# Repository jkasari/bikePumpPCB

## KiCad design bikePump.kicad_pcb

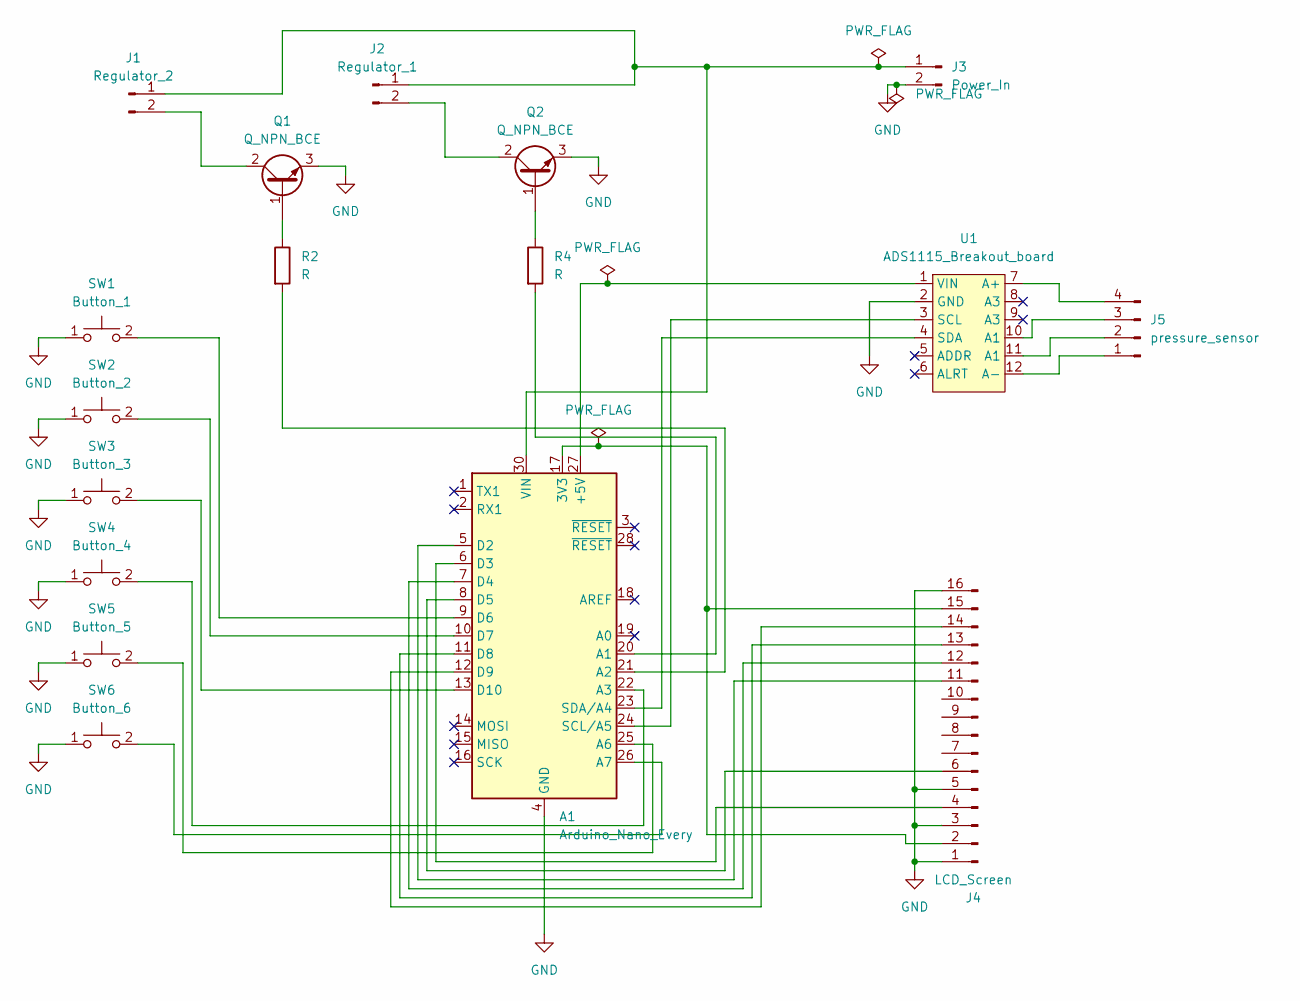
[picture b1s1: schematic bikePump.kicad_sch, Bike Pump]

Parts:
A1: Arduino_Nano_Every; Arduino_Nano
J1: Regulator_2; SolderWire-0.5sqmm_1x02_P4.6mm_D0.9mm_OD2.1mm
J2: Regulator_1; SolderWire-0.5sqmm_1x02_P4.6mm_D0.9mm_OD2.1mm
J3: Power_In; SolderWire-0.5sqmm_1x02_P4.6mm_D0.9mm_OD2.1mm
J4: LCD_Screen
J5: pressure_sensor; SolderWire-0.25sqmm_1x04_P4.5mm_D0.65mm_OD2mm
Q1, Q2: Q_NPN_BCE; DSS60601MZ4-13_NPN_Transitor
R2, R4: R; R_Axial_DIN0207_L6.3mm_D2.5mm_P10.16mm_Horizontal
SW1: Button_1; SW_PUSH_6mm
SW2: Button_2; SW_PUSH_6mm
SW3: Button_3; SW_PUSH_6mm
SW4: Button_4; SW_PUSH_6mm
SW5: Button_5; SW_PUSH_6mm
SW6: Button_6; SW_PUSH_6mm
U1: ADS1115_Breakout_board; AdaFruit_ADS1115_Board

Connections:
GND: A1.4 (GND), A1.29 (GND), J3.2 (+), J4.1, J4.3, J4.5, J4.16, Q1.3 (E), Q2.3 (E), SW1.1, SW2.1 (A), SW3.1, SW4.1, SW5.1, SW6.1, U1.2 (GND); also elsewhere on the board
unnamed 1: A1.5 (D2), J4.11; also elsewhere on the board
unnamed 2: A1.6 (D3), J4.4; also elsewhere on the board
unnamed 3: A1.7 (D4), J4.12; also elsewhere on the board
unnamed 4: A1.8 (D5), J4.6; also elsewhere on the board
unnamed: A1.9 (D6), SW1.2
unnamed: A1.10 (D7), SW2.2
unnamed 7: A1.11 (D8), J4.13; also elsewhere on the board
unnamed 8: A1.12 (D9), J4.14; also elsewhere on the board
unnamed: A1.13 (D10), SW3.2
unnamed 10: A1.17 (3V3), J4.2, J4.15; also elsewhere on the board
unnamed: A1.20 (A1), R4.2
unnamed: A1.21 (A2), R2.2
unnamed: A1.22 (A3), SW4.2
unnamed: A1.23 (SDA/A4), U1.4 (SDA)
unnamed: A1.24 (SCL/A5), U1.3 (SCL)
unnamed: A1.25 (A6), SW5.2
unnamed: A1.26 (A7), SW6.2
unnamed: A1.27 (+5V), U1.1 (VIN)
unnamed: A1.30 (VIN), J1.1, J2.1, J3.1 (-)
unnamed: J2.2, Q2.2 (C)
unnamed: J5.1, U1.12 (A-)
unnamed: J5.2, U1.11 (A1)
unnamed: J5.3, U1.10 (A1)
unnamed: J5.4, U1.7 (A+)
unnamed: Q1.1 (B), R2.1
unnamed: J1.2, Q1.2 (C)
unnamed: Q2.1 (B), R4.1

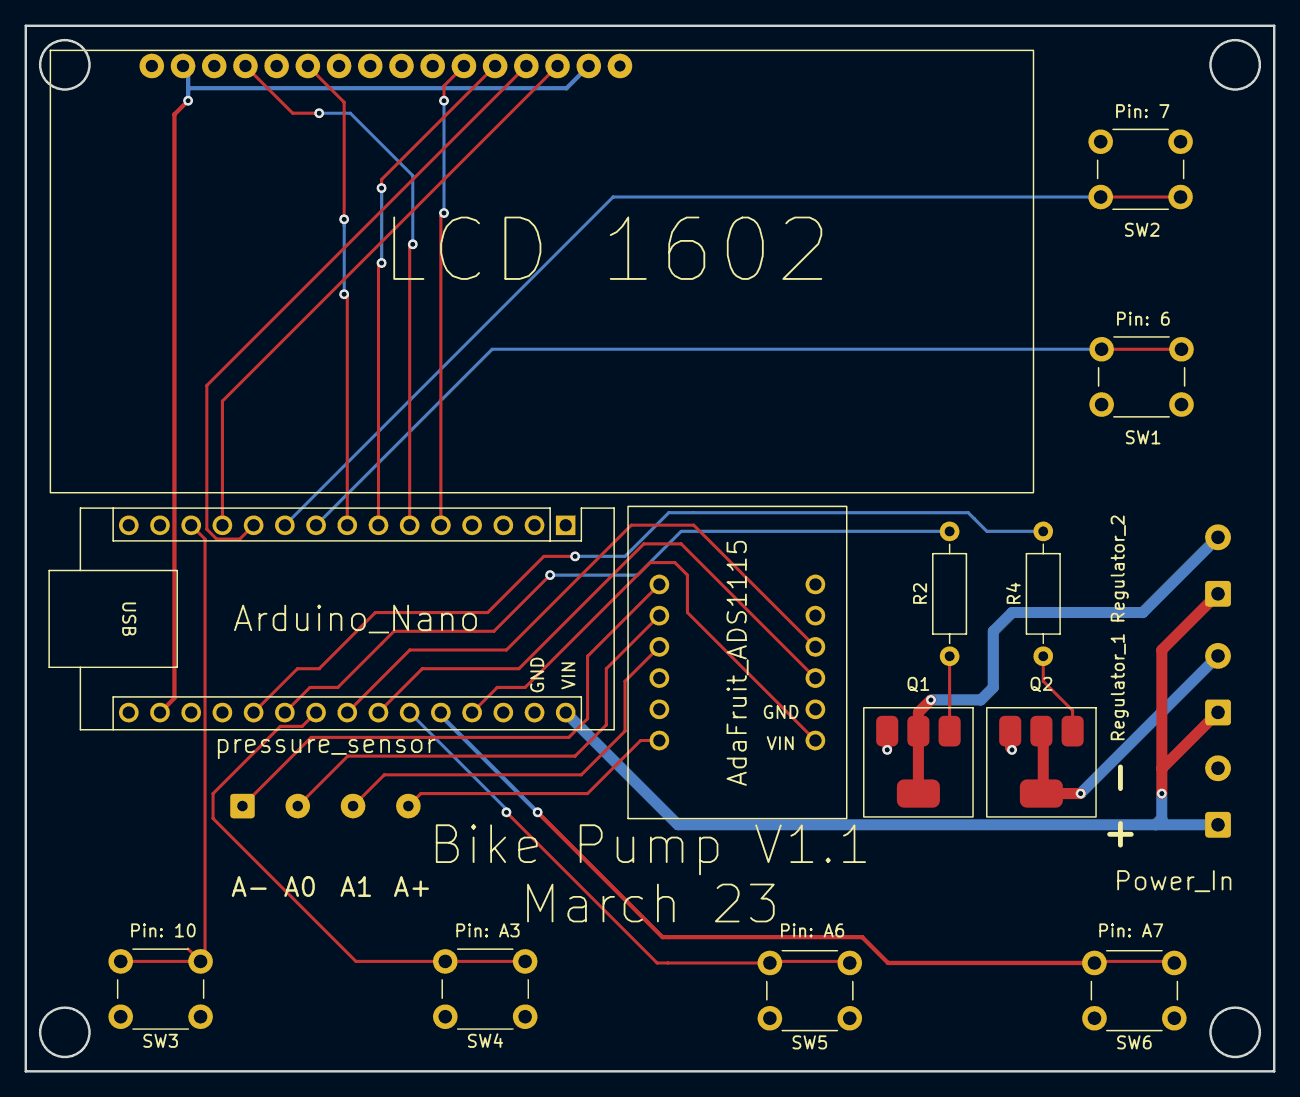
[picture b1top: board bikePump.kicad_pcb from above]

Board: 2 copper layers, 101.6 x 85.1 mm, 17 parts (0 on the bottom side), 28 nets.

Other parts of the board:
LCD 1602: LCD_Screen

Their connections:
GND: LCD 1602.1, LCD 1602.3, LCD 1602.5, LCD 1602.16; also elsewhere on the board
unnamed 1: LCD 1602.11; also elsewhere on the board
unnamed 2: LCD 1602.4; also elsewhere on the board
unnamed 3: LCD 1602.12; also elsewhere on the board
unnamed 4: LCD 1602.6; also elsewhere on the board
unnamed 7: LCD 1602.13; also elsewhere on the board
unnamed 8: LCD 1602.14; also elsewhere on the board
unnamed 10: LCD 1602.2, LCD 1602.15; also elsewhere on the board

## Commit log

2023-03-20 finished silkscreen
2023-03-20 Updated more of the silkscreen
